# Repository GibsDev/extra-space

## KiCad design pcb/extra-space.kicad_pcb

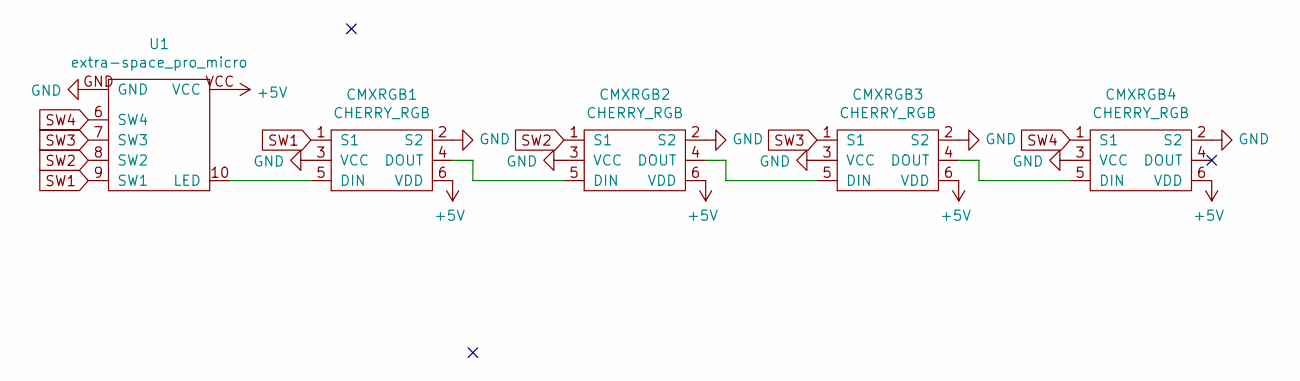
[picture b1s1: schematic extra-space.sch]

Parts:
CMXRGB1, CMXRGB2, CMXRGB3, CMXRGB4: CHERRY_RGB
U1: extra-space_pro_micro

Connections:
+5V: CMXRGB1.6 (VDD), CMXRGB2.6 (VDD), CMXRGB3.6 (VDD), CMXRGB4.6 (VDD), U1.VCC
GND: CMXRGB1.2 (S2), CMXRGB1.3 (VCC), CMXRGB2.2 (S2), CMXRGB2.3 (VCC), CMXRGB3.2 (S2), CMXRGB3.3 (VCC), CMXRGB4.2 (S2), CMXRGB4.3 (VCC), U1.GND
unnamed: CMXRGB1.4 (DOUT), CMXRGB2.5 (DIN)
unnamed: CMXRGB1.5 (DIN), U1.10 (LED)
unnamed: CMXRGB2.4 (DOUT), CMXRGB3.5 (DIN)
unnamed: CMXRGB3.4 (DOUT), CMXRGB4.5 (DIN)
SW1: CMXRGB1.1 (S1), U1.9 (SW1)
SW2: CMXRGB2.1 (S1), U1.8 (SW2)
SW3: CMXRGB3.1 (S1), U1.7 (SW3)
SW4: CMXRGB4.1 (S1), U1.6 (SW4)

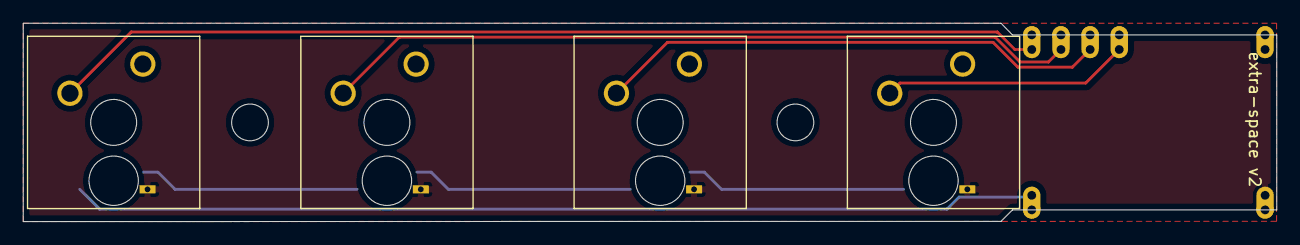
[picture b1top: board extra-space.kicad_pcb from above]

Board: 2 copper layers, 109.2 x 17.3 mm, 5 parts (0 on the bottom side), 10 nets.

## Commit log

2021-11-08 added README
